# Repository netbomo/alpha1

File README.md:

alpha1
======

Prototype de shield pour arduino, permettant de monitorer une éolienne.

Voir les premières données :

http://desplanchesdepalette.org/colibri/Colibri_Energie.html

Projet :
--------

Le but est de créer une shield pouvant par exemple créer un node pour le système OpenEnergyMonitor ou se greffant sur une carte Akeru, une carte Arduino Yun...

###Capteur désirés :

- Anémomètre
- girouette
- capteur de courant
- capteur de tension 

note : Pour l'instant ma carte emontx ne fontionne plus, et la sonde de courant CT ne donne plus de valeur correcte, donc nous utilisons un WattNode Pulse ainsi qu'une carte arduino UNO.

###Etat des lieux :
 Le systême fonctionne à l'atelier, mais pose problème en situation, la présence proche du réseau à l'air d'en être la cause. La prochaine modification sera de mettre le systême dans un boitier métalique avec une mise à la masse. Une carte de meilleure qualité devrait aider aussi.

Le premier prototype est installé avec la version du programme netbomo.ino

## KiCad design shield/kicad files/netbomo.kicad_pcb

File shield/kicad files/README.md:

## Lots of bugs on this card, please don't use it!

### Netbomo schematic :

The "WIND1" and the "WIND2" are composed of 2 op-amp circuits :
  - the first one amplifies "sinusoidal" data coming from the NRG-type anemometers
  - the second one convert it to a square wave curve that can be used afterward to count RPMs

### Netbomo board :

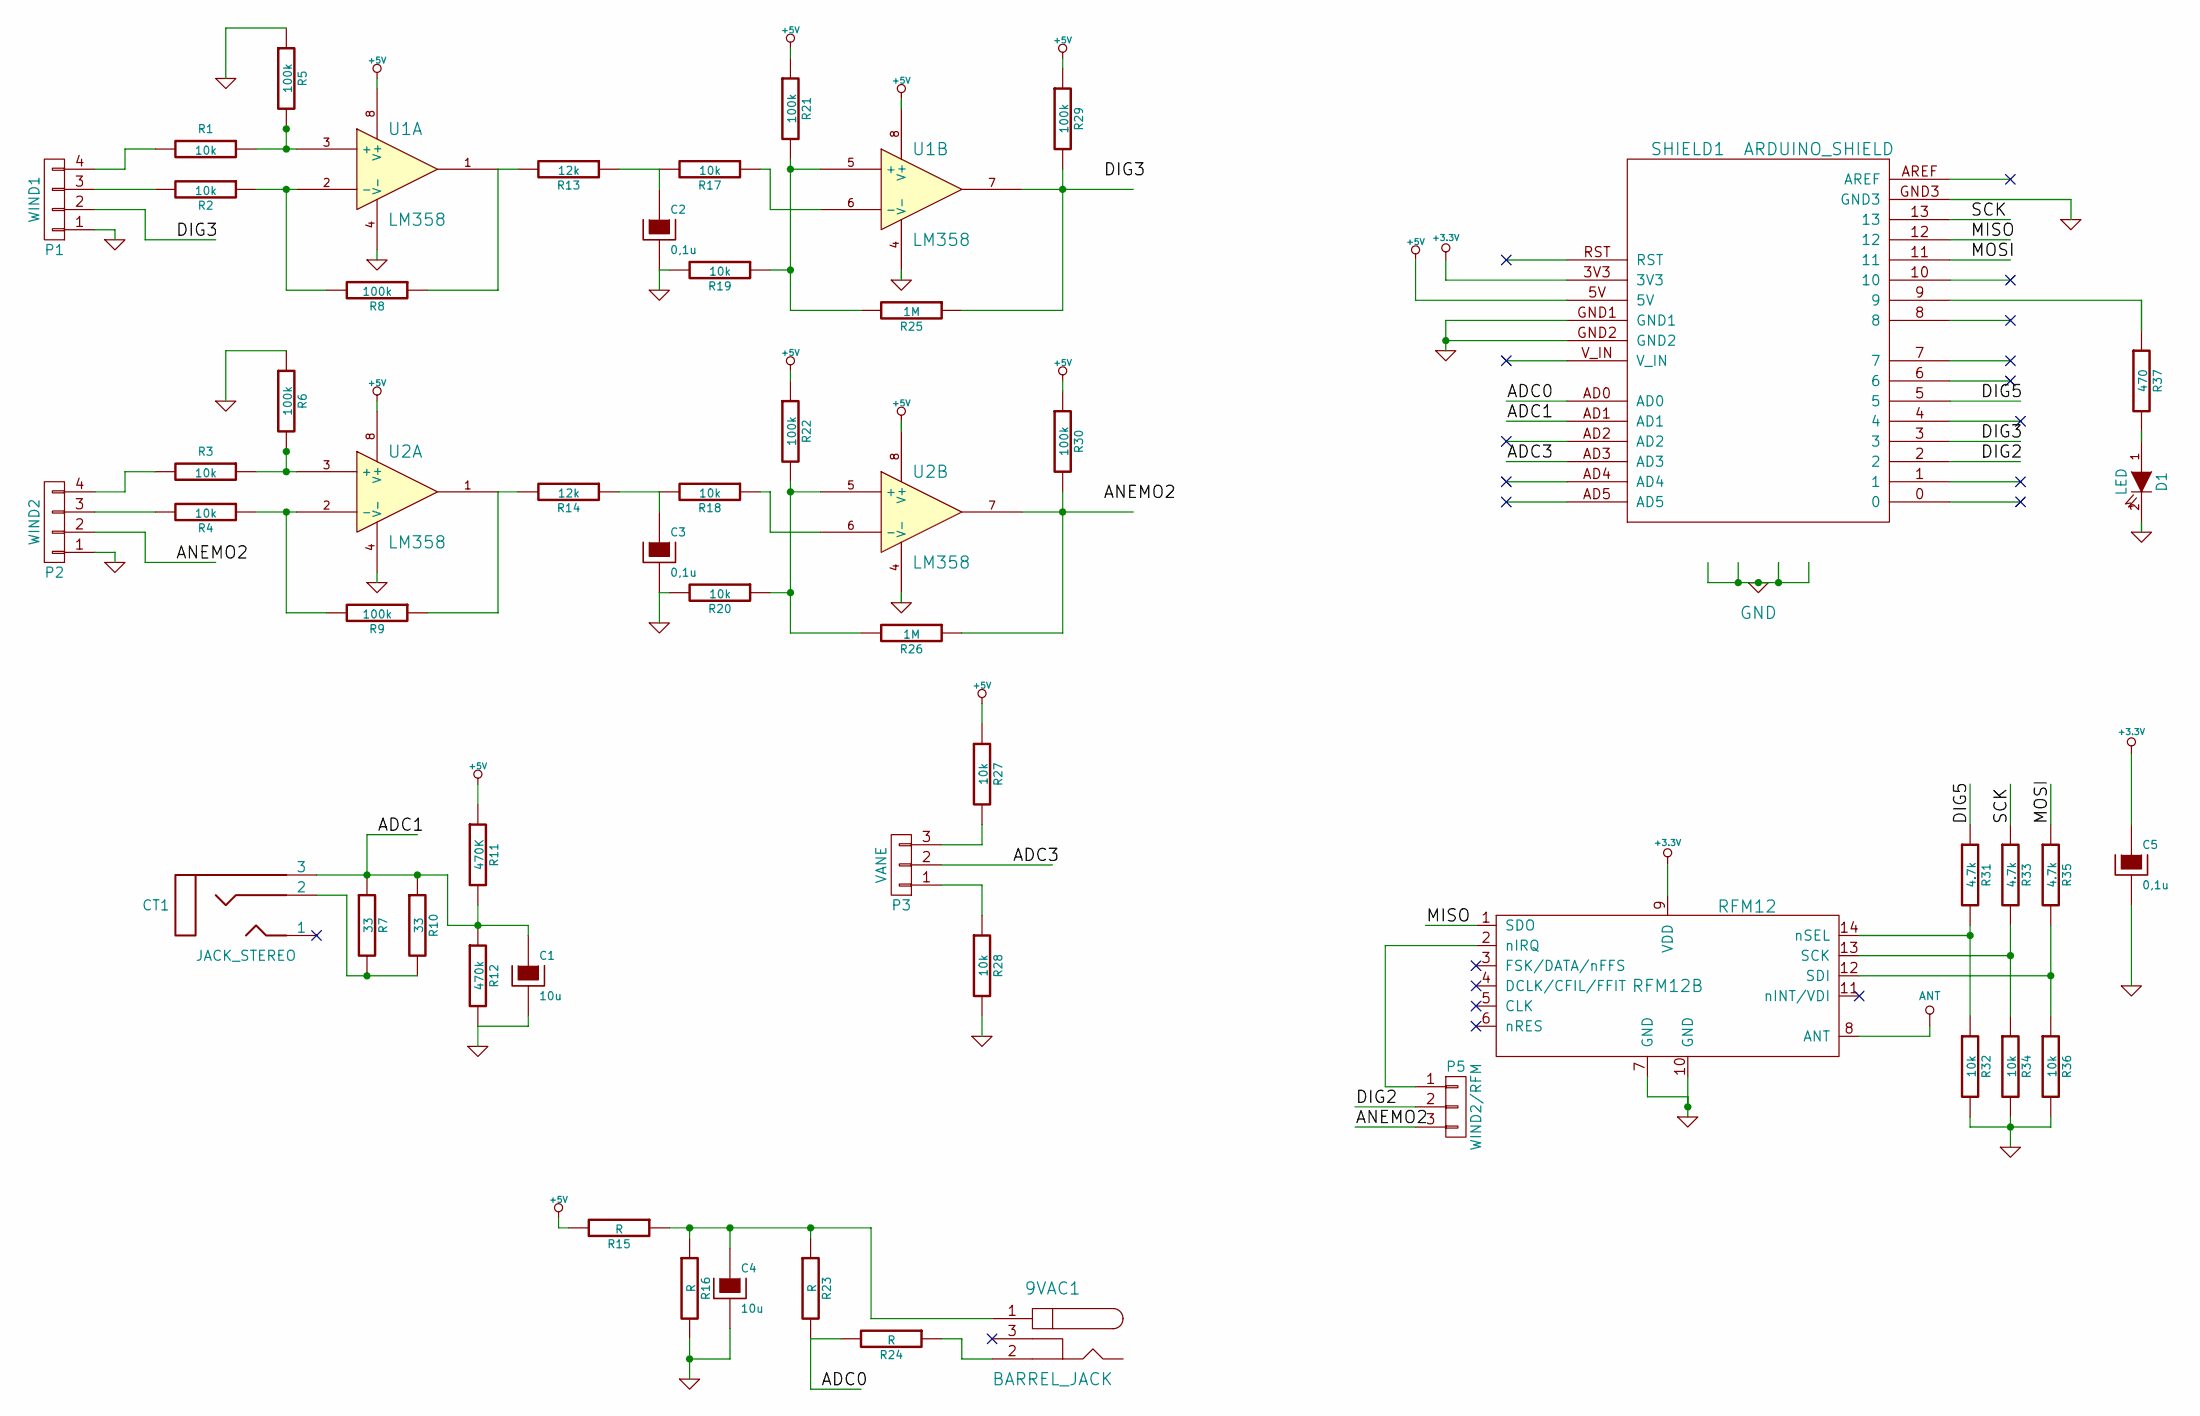
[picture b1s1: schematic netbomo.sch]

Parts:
9VAC1: BARREL_JACK
C1, C4: 10u; c_elec_4x5.3
C2, C3, C5: 0,1u; c_elec_4x5.3
CT1: JACK_STEREO; JACK_2.1_DC
D1: LED; Diode-MiniMELF_Standard
P1: WIND1; BORNIER_04
P2: WIND2; BORNIER_04
P3: VANE; BORNIER_03
P5: WIND2/RFM; PAD_3
R1, R2, R3, R4, R17, R18, R19, R20, R27, R28, R32, R34, R36: 10k; R_1206
R5, R6, R8, R9, R21, R22, R29, R30: 100k; R_1206
R7, R10: 33; R_1206
R11: 470K; R_1206
R12: 470k; R_1206
R13, R14: 12k; R_1206
R15, R16, R23, R24: R; R_1206
R25, R26: 1M; R_1206
R31, R33, R35: 4.7k; R_1206
R37: 470; R_1206
RFM12: RFM12
SHIELD1: ARDUINO_SHIELD; ARDUINO_SHIELD_2
U1, U2: LM358; DIP-8__300_ELL

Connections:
+3.3V: C5.1, RFM12.9 (VDD), SHIELD1.3V3; also elsewhere on the board
+5V: R11.1, R15.2, R21.1, R22.1, R27.1, R29.1, R30.1, SHIELD1.5V, U1.8 (V+), U2.8 (V+); also elsewhere on the board
/ADC0: R23.2, R24.2, SHIELD1.AD0; also elsewhere on the board
/ADC1: C1.1, CT1.3, R7.1, R10.1, R11.2, R12.1, SHIELD1.AD1; also elsewhere on the board
/ADC3: P3.2, SHIELD1.AD3; also elsewhere on the board
/ANEMO2: P2.2, P5.3
/DIG2: P5.2, SHIELD1.2; also elsewhere on the board
/DIG3: P1.2, SHIELD1.3; also elsewhere on the board
/DIG5: R31.1, SHIELD1.5; also elsewhere on the board
/MISO: RFM12.1 (SDO), SHIELD1.12; also elsewhere on the board
/MOSI: R35.1, SHIELD1.11; also elsewhere on the board
/SCK: R33.1, SHIELD1.13; also elsewhere on the board
GND: C1.2, C2.2, C3.2, C4.2, C5.2, D1.2 (K), P1.1, P2.1, R5.1, R6.1, R12.2, R16.2, R19.2, R20.2, R28.2, R32.2, R34.2, R36.2, RFM12.7 (GND), RFM12.10 (GND), SHIELD1.GND1, SHIELD1.GND2, SHIELD1.GND3, U1.4 (V-), U2.4 (V-); also elsewhere on the board
unnamed 13: 9VAC1.1, C4.1, R15.1, R16.1, R23.1; also elsewhere on the board
unnamed 14: 9VAC1.2, R24.1; also elsewhere on the board
unnamed: C2.1, R13.1, R17.2
unnamed: C3.1, R14.1, R18.2
unnamed: CT1.2, R7.2, R10.2
unnamed: D1.1 (A), R37.2
unnamed: P1.3, R2.2
unnamed: P1.4, R1.2
unnamed: P2.3, R4.2
unnamed: P2.4, R3.2
unnamed: P3.1, R28.1
unnamed: P3.3, R27.2
unnamed: P5.1, RFM12.2 (nIRQ)
unnamed: R1.1, R5.2, U1.3 (+)
unnamed: R2.1, R8.2, U1.2 (-)
unnamed: R3.1, R6.2, U2.3 (+)
unnamed: R4.1, R9.2, U2.2 (-)
unnamed: R8.1, R13.2, U1.1
unnamed: R9.1, R14.2, U2.1
unnamed: R17.1, U1.6 (-)
unnamed: R18.1, U2.6 (-)
unnamed: R19.1, R21.2, R25.2, U1.5 (+)
unnamed: R20.1, R22.2, R26.2, U2.5 (+)
unnamed: R25.1, R29.2, U1.7
unnamed: R26.1, R30.2, U2.7
unnamed: R31.2, R32.1, RFM12.14 (nSEL)
unnamed: R33.2, R34.1, RFM12.13 (SCK)
unnamed: R35.2, R36.1, RFM12.12 (SDI)
unnamed 43: R37.1, SHIELD1.9; also elsewhere on the board
VPP: RFM12.8 (ANT)

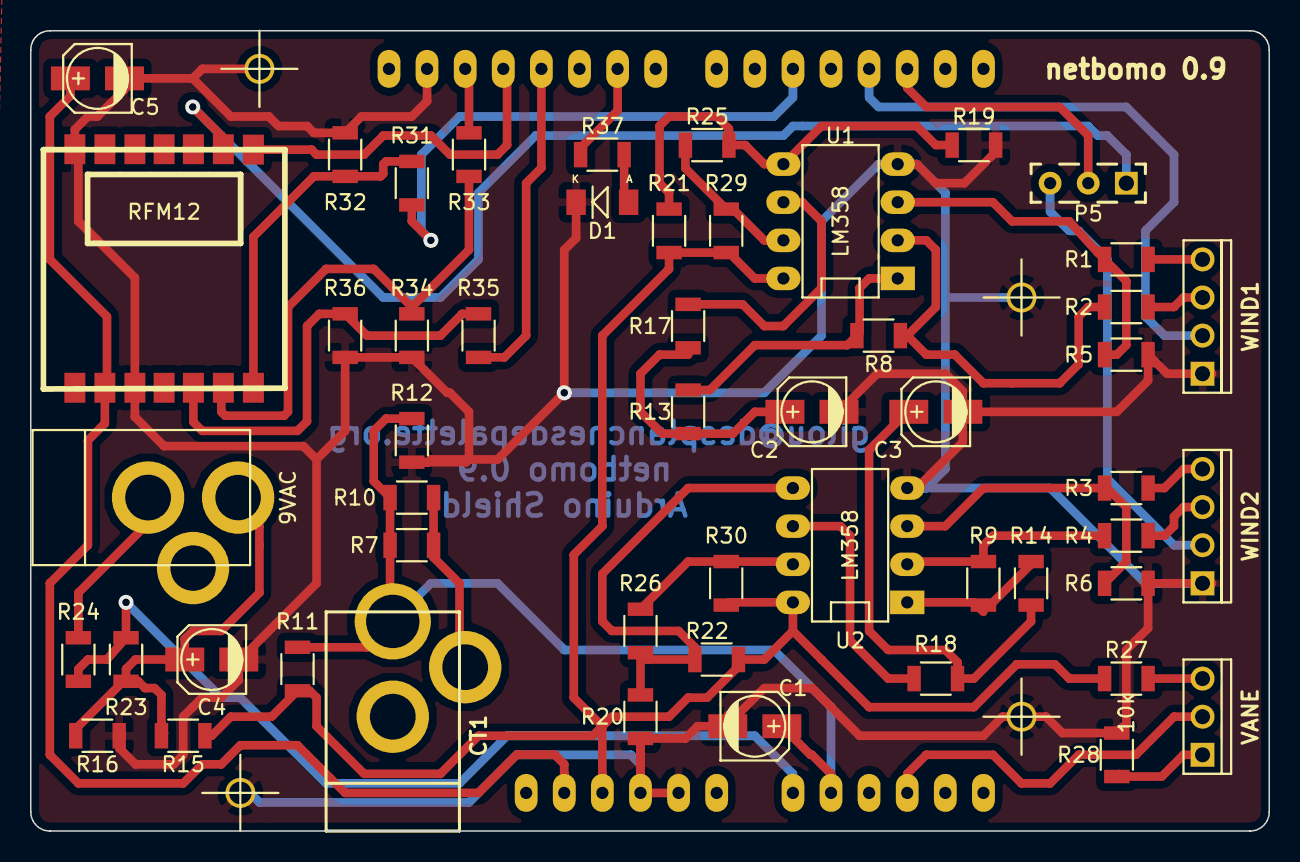
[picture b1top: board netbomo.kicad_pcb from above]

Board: 2 copper layers, 82.6 x 53.3 mm, 53 parts (0 on the bottom side), 42 nets.

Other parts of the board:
9VAC: BARREL_JACK
netbomo 0.9: ARDUINO_SHIELD; ARDUINO_SHIELD_2

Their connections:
+3.3V: netbomo 0.9.3V3; also elsewhere on the board
+5V: netbomo 0.9.5V; also elsewhere on the board
/ADC0: netbomo 0.9.AD0; also elsewhere on the board
/ADC1: netbomo 0.9.AD1; also elsewhere on the board
/ADC3: netbomo 0.9.AD3; also elsewhere on the board
/DIG2: netbomo 0.9.2; also elsewhere on the board
/DIG3: netbomo 0.9.3; also elsewhere on the board
/DIG5: netbomo 0.9.5; also elsewhere on the board
/MISO: netbomo 0.9.12; also elsewhere on the board
/MOSI: netbomo 0.9.11; also elsewhere on the board
/SCK: netbomo 0.9.13; also elsewhere on the board
GND: netbomo 0.9.GND1, netbomo 0.9.GND2, netbomo 0.9.GND3; also elsewhere on the board
unnamed 13: 9VAC.1; also elsewhere on the board
unnamed 14: 9VAC.2; also elsewhere on the board
unnamed 43: netbomo 0.9.9; also elsewhere on the board

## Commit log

2014-06-20 edit README.md
2014-06-20 add Raspberry conf
2014-06-20 edit raspberryConf/README.md
2014-06-20 test
2014-06-20 init commit
2014-06-20 summit
2014-06-20 add 3Gtest
2014-06-24 add schematic
2014-07-04 add netbomo ino
2014-08-08 The windWane representation has been modified
2014-12-04 clean in repositories
2014-12-04 Updade *.ino
2014-12-04 Add Display files
2014-12-16 update kicad files
2015-03-13 test yasin
